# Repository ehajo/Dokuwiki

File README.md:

Zur Dokumentation der alten Bausätze habe ich hier das alte Dokuwiki so gut wie möglich übernommen:

[Wiki](https://github.com/ehajo/Dokuwiki/wiki)

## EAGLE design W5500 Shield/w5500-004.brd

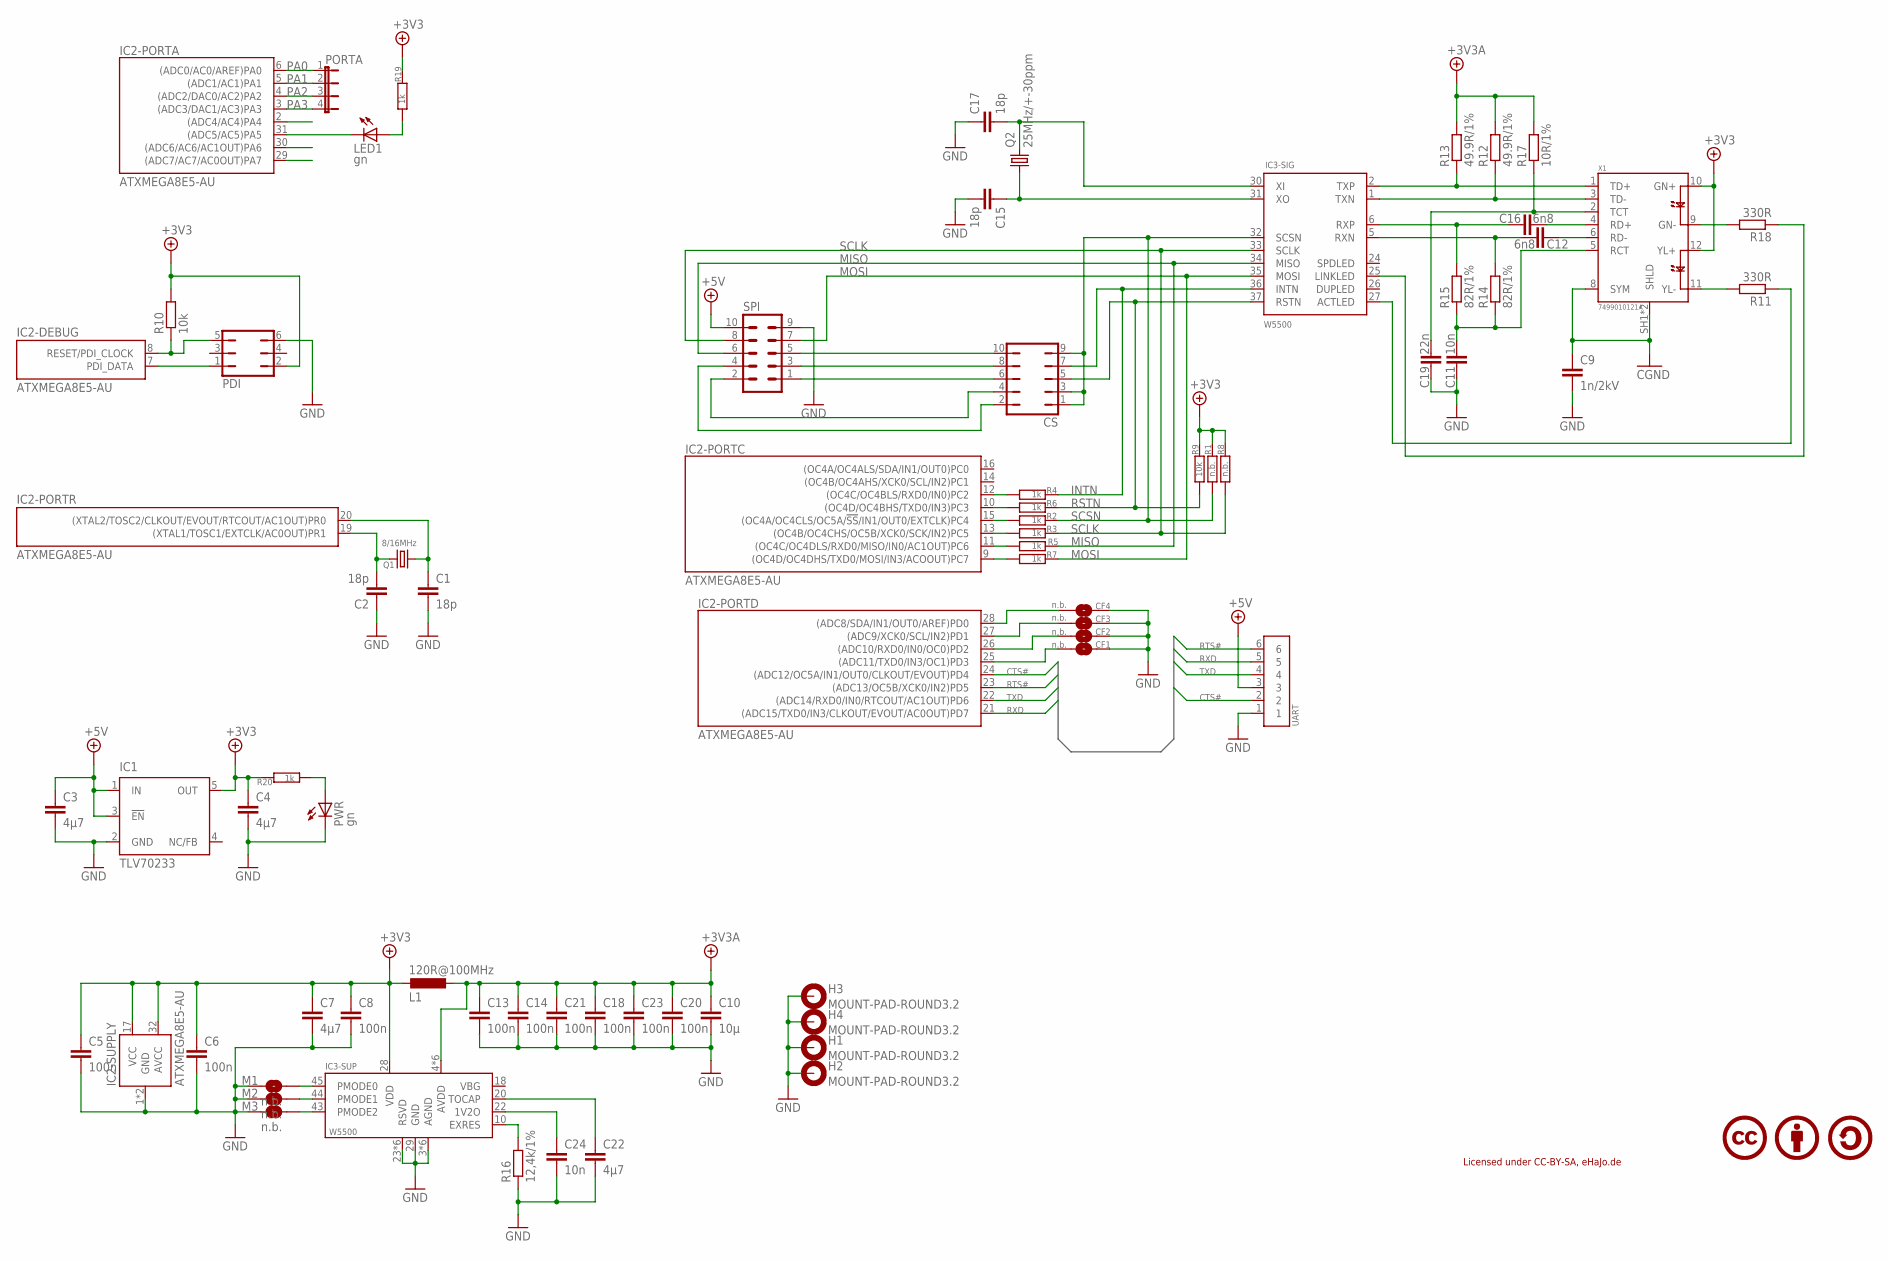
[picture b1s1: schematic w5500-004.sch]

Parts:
C1, C2, C15, C17: 18p; C0603
C3, C4, C7, C22: 4µ7; C0805
C5, C6, C8, C13, C14, C18, C20, C21, C23: 100n; C0603
C9: 1n/2kV; C0805
C10: 10µ; C1206
C11, C24: 10n; C0603
C12, C16: 6n8; C0603
C19: 22n; C0603
CF1, CF2, CF3, CF4: n.b.; SJS
CS: JP5Q
H1, H2, H3, H4: MOUNT-PAD-ROUND3.2; 3,2-PAD
IC1: TLV70233; SOT23-DBV
IC2: ATXMEGA8E5-AU; TQFP32-08
IC3: W5500; LQFP48
L1: 120R@100MHz; R0805
LED1: gn; CHIP-LED0805
M1, M2, M3: n.b.; SJS
PDI: JP3Q
PORTA: JP4ESML; 4SML
PWR: gn; CHIP-LED0805
Q1: 8/16MHz; HC49U70
Q2: 25MHz/+-30ppm; HC49U70
R1, R8: n.b.; R0603
R2, R3, R4, R5, R6, R7, R19, R20: 1k; R0603
R9, R10: 10k; R0603
R11, R18: 330R; R0603
R12, R13: 49.9R/1%; R0603
R14, R15: 82R/1%; R0603
R16: 12,4k/1%; R0603
R17: 10R/1%; R0603
SPI: ML10
UART: JP6E
X1: 7499010121A; 121A

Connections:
+3V3: C4.1, C5.1, C6.1, C7.1, C8.1, IC1.5 (OUT), IC2.17 (VCC), IC2.32 (AVCC), IC3.28 (VDD), L1.2, PDI.2, R1.2, R8.2, R9.2, R10.2, R19.2, R20.2, X1.10 (GN+), X1.12 (YL+)
+3V3A: C10.1, C13.1, C14.1, C18.1, C20.1, C21.1, C23.1, IC3.4 (AVDD), IC3.8 (AVDD), IC3.11 (AVDD), IC3.15 (AVDD), IC3.17 (AVDD), IC3.21 (AVDD), L1.1, R12.2, R13.2, R17.2
+5V: C3.1, IC1.1 (IN), IC1.3 (!EN), SPI.10, UART.3
CGND: C9.1, X1.8 (SYM), X1.SH1 (SHLD), X1.SH2 (SHLD)
CS1: CS.6, SPI.1
CS2: CS.4, SPI.2
CS3: CS.8, SPI.3
CS4: CS.2, SPI.4
CTS#: IC2.24 ((ADC12/OC5A/IN1/OUT0/CLKOUT/EVOUT)PD4), UART.2
GND: C1.2, C2.1, C3.2, C4.2, C5.2, C6.2, C7.2, C8.2, C9.2, C10.2, C11.1, C13.2, C14.2, C15.2, C17.1, C18.2, C19.1, C20.2, C21.2, C22.2, C23.2, C24.2, CF1.2, CF2.2, CF3.2, CF4.2, H1.B3,2, H2.B3,2, H3.B3,2, H4.B3,2, IC1.2 (GND), IC2.1 (GND), IC2.18 (GND), IC3.3 (AGND), IC3.9 (AGND), IC3.14 (AGND), IC3.16 (AGND), IC3.19 (AGND), IC3.23 (RSVD), IC3.29 (GND), IC3.38 (RSVD), IC3.39 (RSVD), IC3.40 (RSVD), IC3.41 (RSVD), IC3.42 (RSVD), IC3.48 (AGND), M1.1, M2.1, M3.1, PDI.6, PWR.C, R16.1, SPI.9, UART.1
INTN: CS.7, IC3.36 (INTN), R4.1
MISO: IC3.34 (MISO), R5.1, SPI.6
MOSI: IC3.35 (MOSI), R7.1, SPI.7
unnamed: IC3.10 (EXRES), R16.2
unnamed: C24.1, IC3.22 (1V2O)
unnamed: C22.1, IC3.20 (TOCAP)
unnamed: IC3.45 (PMODE0), M1.2
unnamed: R18.2, X1.9 (GN-)
unnamed: IC3.44 (PMODE1), M2.2
unnamed: IC3.43 (PMODE2), M3.2
unnamed: C15.1, IC3.31 (XO), Q2.1
unnamed: C17.2, IC3.30 (XI), Q2.2
unnamed: IC2.8 (RESET/PDI_CLOCK), PDI.5, R10.1
unnamed: IC2.11 ((OC4C/OC4DLS/RXD0/MISO/IN0/AC1OUT)PC6), R5.2
unnamed: IC2.12 ((OC4C/OC4BLS/RXD0/IN0)PC2), R4.2
unnamed: IC2.15 ((OC4A/OC4CLS/OC5A/!SS!/IN1/OUT0/EXTCLK)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), R2.2
unnamed: IC2.9 ((OC4D/OC4DHS/TXD0/MOSI/IN3/ACOOUT)PC7), R7.2
unnamed: IC2.13 ((OC4B/OC4CHS/OC5B/XCK0/SCK/IN2)PC5), R3.2
unnamed: CF4.1, IC2.28 ((ADC8/SDA/IN1/OUT0/AREF)PD0)
unnamed: CF3.1, IC2.27 ((ADC9/XCK0/SCL/IN2)PD1)
unnamed: IC2.10 ((OC4D/OC4BHS/TXD0/IN3)PC3), R6.2
unnamed: CF2.1, IC2.26 ((ADC10/RXD0/IN0/OC0)PD2)
unnamed: IC2.7 (PDI_DATA), PDI.1
unnamed: CF1.1, IC2.25 ((ADC11/TXD0/IN3/OC1)PD3)
unnamed: C16.2, X1.4 (RD+)
unnamed: C12.1, X1.6 (RD-)
unnamed: C11.2, R14.1, R15.1, X1.5 (RCT)
unnamed: C19.2, R17.1, X1.2 (TCT)
unnamed: R11.2, X1.11 (YL-)
unnamed: IC3.27 (ACTLED), R11.1
unnamed: IC3.25 (LINKLED), R18.1
unnamed: IC2.31 ((ADC5/AC5)PA5), LED1.C
unnamed: C2.2, IC2.19 ((XTAL1/TOSC1/EXTCLK/AC0OUT)PR1), Q1.1
unnamed: C1.1, IC2.20 ((XTAL2/TOSC2/CLKOUT/EVOUT/RTCOUT/AC1OUT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), Q1.2
unnamed: PWR.A, R20.1
unnamed: LED1.A, R19.1
PA0: IC2.6 ((ADC0/AC0/AREF)PA0), PORTA.1
PA1: IC2.5 ((ADC1/AC1)PA1), PORTA.2
PA2: IC2.4 ((ADC2/DAC0/AC2)PA2), PORTA.3
PA3: IC2.3 ((ADC3/DAC1/AC3)PA3), PORTA.4
RSTN: CS.5, IC3.37 (RSTN), R6.1, R9.1
RTS#: IC2.23 ((ADC13/OC5B/XCK0/IN2)PD5), UART.6
RX+: C16.1, IC3.6 (RXP), R15.2
RX-: C12.2, IC3.5 (RXN), R14.2
RXD: IC2.21 ((ADC15/TXD0/IN3/CLKOUT/EVOUT/AC0OUT)PD7), UART.5
SCLK: IC3.33 (SCLK), R3.1, R8.1, SPI.8
SCSN: CS.1, CS.3, CS.9, IC3.32 (SCSN), R1.1, R2.1
SS: CS.10, SPI.5
TD+: IC3.2 (TXP), R13.1, X1.1 (TD+)
TD-: IC3.1 (TXN), R12.1, X1.3 (TD-)
TXD: IC2.22 ((ADC14/RXD0/IN0/RTCOUT/AC1OUT)PD6), UART.4

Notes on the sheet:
Licensed under CC-BY-SA, eHaJo.de

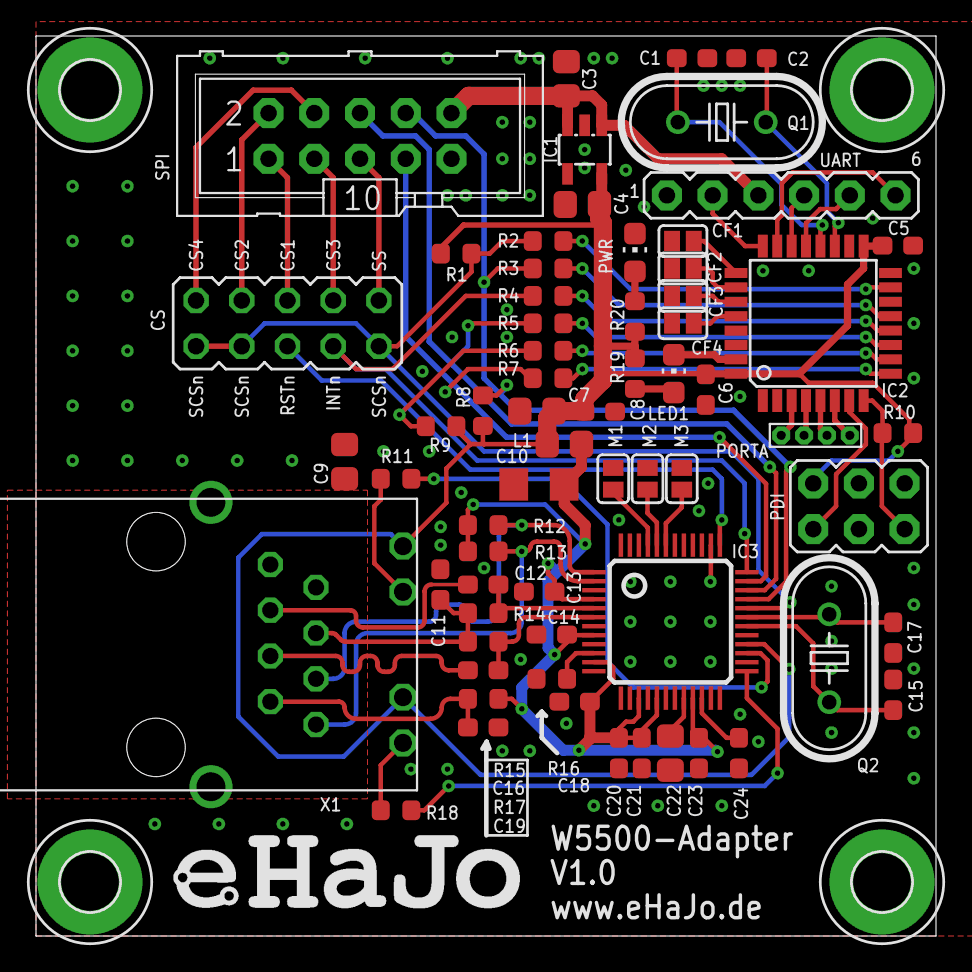
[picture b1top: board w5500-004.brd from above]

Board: 2 copper layers, 50.0 x 50.0 mm, 69 parts (0 on the bottom side), 61 nets.

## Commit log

2025-01-10 iniitial commit
2025-01-10 initial
2025-01-10 iniital commit
2025-02-27 initial commit
    Software für aTeVaL basierend auf LUFA-Stack
